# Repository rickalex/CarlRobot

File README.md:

# CarlRobot
A robot named Carl built in a Comm Tech class.

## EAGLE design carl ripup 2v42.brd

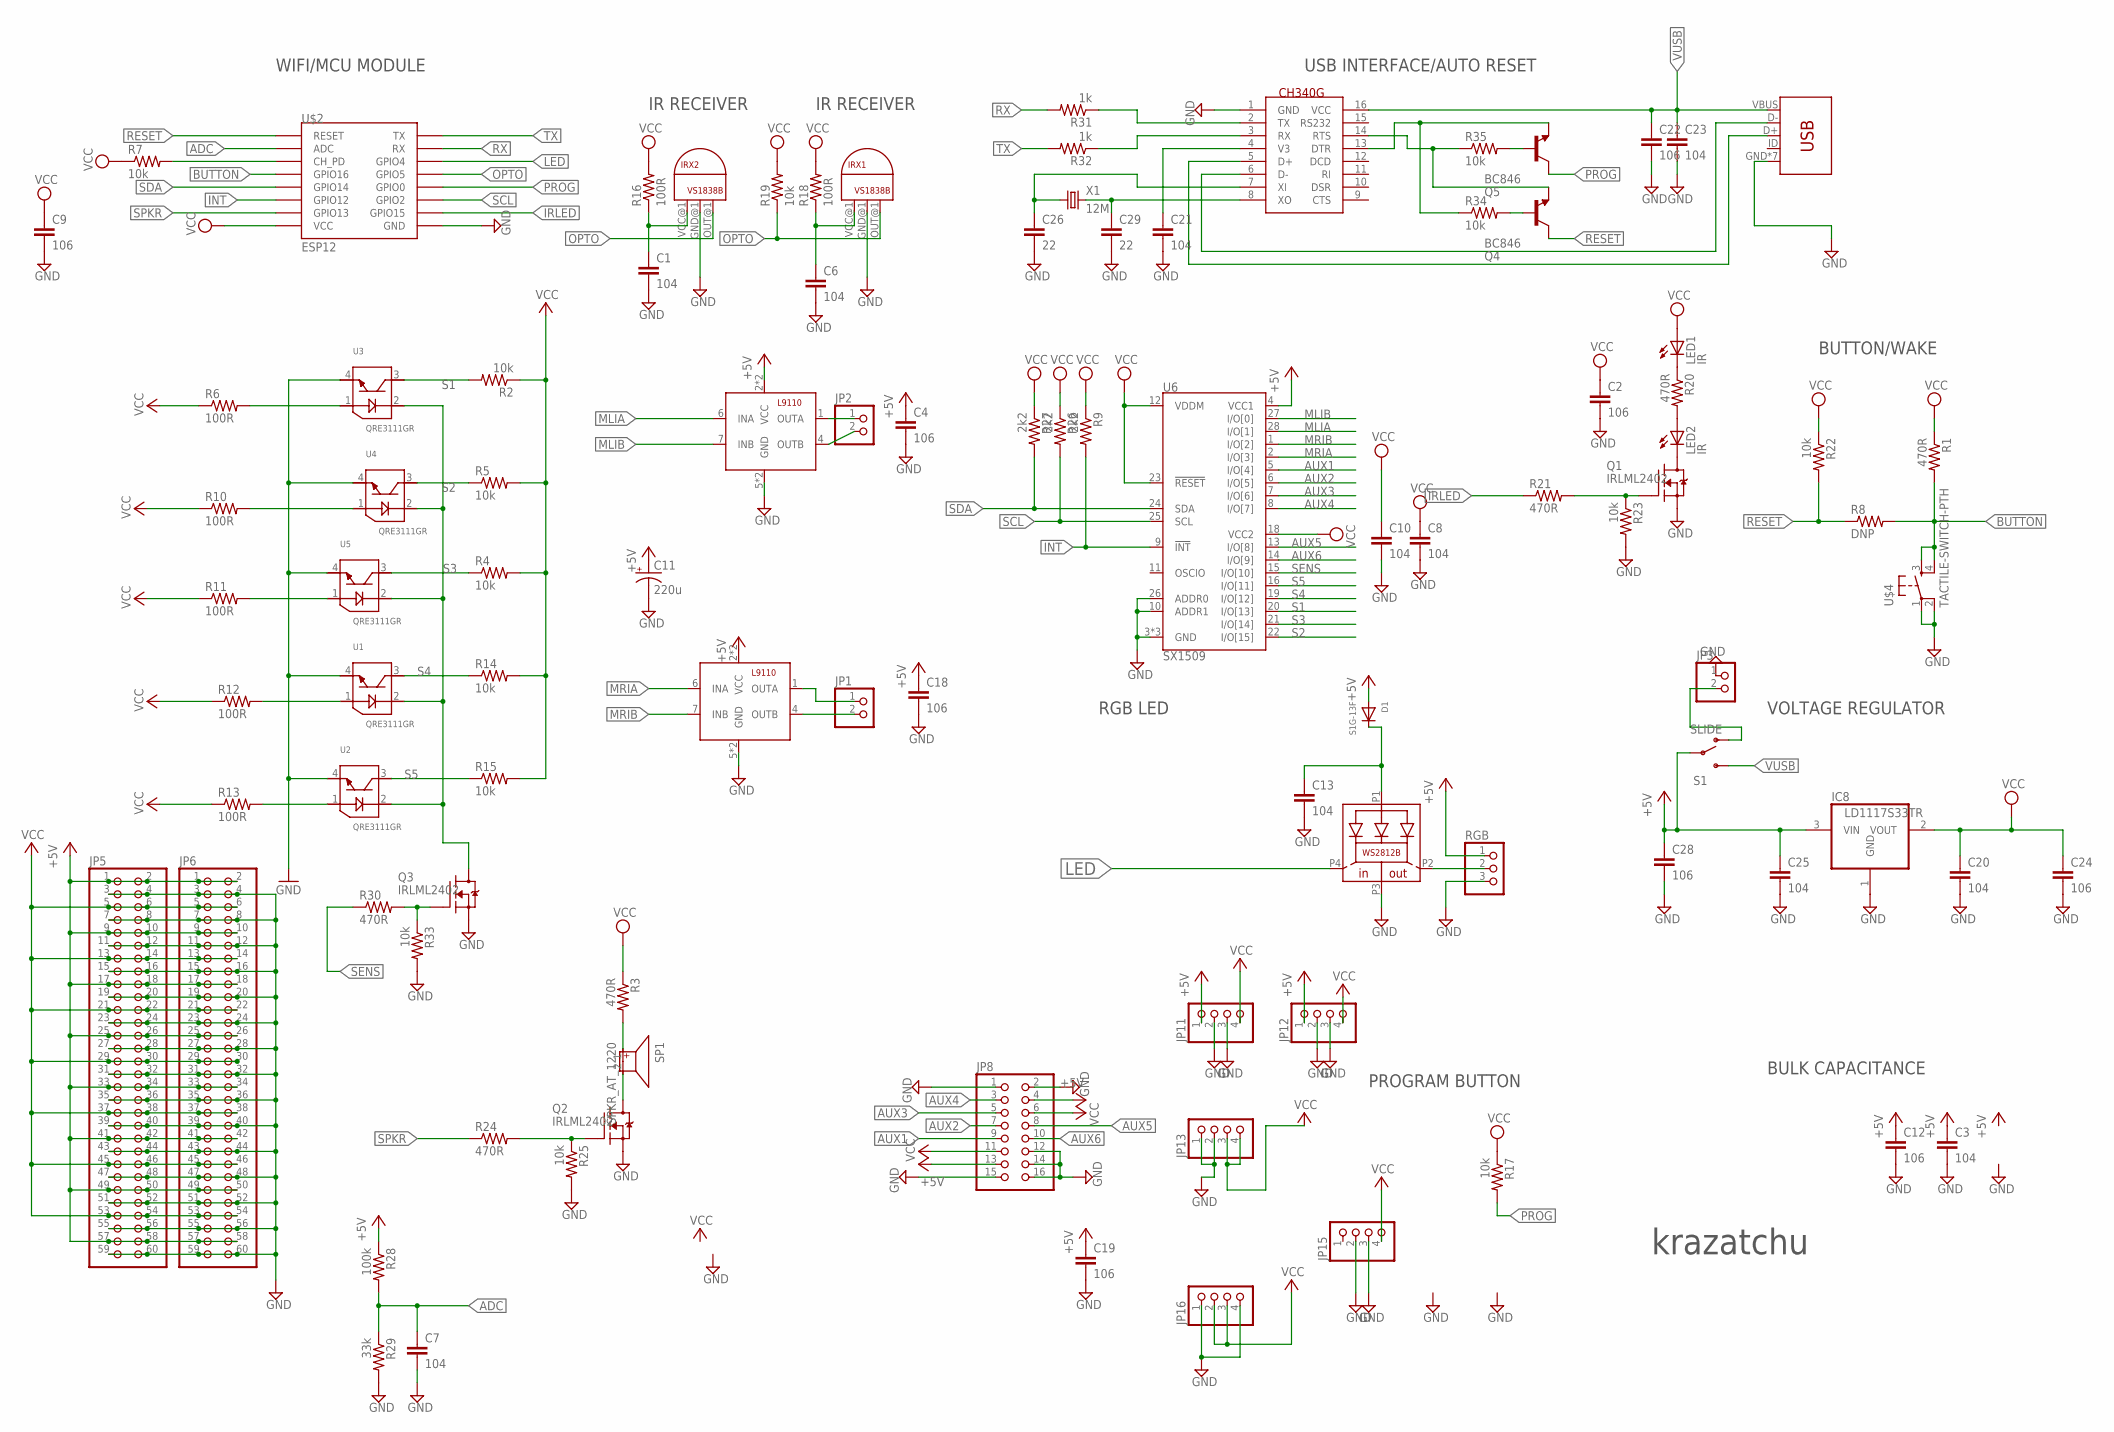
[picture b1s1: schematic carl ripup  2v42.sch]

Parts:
C1, C3, C6, C7, C8, C10, C13, C20, C21, C23, C25: 104; C0805
C2, C4, C9, C12, C18, C19, C22, C24, C28: 106; C0805
C11: 220u; 140CLH-0810
C26, C29: 22; C0805
D1: S1G-13F; SMADIODE
IC1, IC2: L9110; SOIC8
IC8: LD1117S33TR; SOT223
IRX1, IRX2: VS1838B; IR-RX-SINGLE
JP1, JP2, JP3: PINHD-1X2; 1X02
JP5, JP6: PINHD-2X30; 2X30
JP8: PINHD-2X8; 2X08
JP11, JP12, JP13, JP15, JP16: PINHD-1X4; 1X04
LED1, LED2: IR; LED5MM
Q1, Q2, Q3: IRLML2402; SOT23
Q4, Q5: BC846; SOT23
R1, R3, R20, R21, R24, R30: 470R; R0805
R2, R4, R5, R7, R14, R15, R17, R19, R22, R23, R25, R33, R34, R35: 10k; R0805
R6, R10, R11, R12, R13, R16, R18: 100R; R0805
R8: DNP; R0805
R9, R26, R27: 2k2; R0805
R28: 100k; R0805
R29: 33k; R0805
R31, R32: 1k; R0805
RGB: PINHD-1X3RND; 1X03_ROUND
RGB1: ws2812b; PLCC_4_5050_TRIM
S1: SLIDE; SWITCH-SPDT
SP1: SPKR_AT_1220; TRANSDUCER_12/6
U1, U2, U3, U4, U5: QRE3111GR; QRE1113GR
U6: SX1509; QFN-28
U$2: ESP12
U$4: TACTILE-SWITCH-PTH; TAC-SWITCH-PTH
U$5: CH340G; SOIC16
USB1: USB_MICROB-10118194-0001LF; USB-MICRO-B
X1: 12M; HC49UP

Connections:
+5V: C3.1, C4.1, C11.+, C12.1, C18.1, C19.1, C25.1, C28.1, D1.A, IC1.2 (VCC), IC1.3 (VCC), IC2.2 (VCC), IC2.3 (VCC), IC8.3 (VIN), JP5.1, JP5.2, JP5.9, JP5.10, JP5.17, JP5.18, JP5.25, JP5.26, JP5.33, JP5.34, JP5.41, JP5.42, JP5.49, JP5.50, JP5.57, JP5.58, JP6.1, JP6.2, JP6.9, JP6.10, JP6.17, JP6.18, JP6.25, JP6.26, JP6.33, JP6.34, JP6.41, JP6.42, JP6.49, JP6.50, JP6.57, JP6.58, JP8.4, JP8.13, JP11.1, JP12.1, R28.1, RGB.1, S1.2, U6.4 (VCC1)
ADC: C7.1, R28.2, R29.1, U$2.ADC
AUX1: JP8.9, U6.5 (I/O[4])
AUX2: JP8.7, U6.6 (I/O[5])
AUX3: JP8.5, U6.7 (I/O[6])
AUX4: JP8.3, U6.8 (I/O[7])
AUX5: JP8.8, U6.13 (I/O[8])
AUX6: JP8.10, U6.14 (I/O[9])
BUTTON: R1.2, R8.2, U$2.GPIO16, U$4.3, U$4.4
GND: C1.2, C2.2, C3.2, C4.2, C6.2, C7.2, C8.2, C9.2, C10.2, C11.-, C12.2, C13.2, C18.2, C19.2, C20.2, C21.2, C22.2, C23.2, C24.2, C25.2, C26.2, C28.2, C29.2, IC1.5 (GND), IC1.8 (GND), IC2.5 (GND), IC2.8 (GND), IC8.1 (GND), IRX1.GND@1 (GND), IRX2.GND@1 (GND), JP3.1, JP5.3, JP5.4, JP5.7, JP5.8, JP5.11, JP5.12, JP5.15, JP5.16, JP5.19, JP5.20, JP5.23, JP5.24, JP5.27, JP5.28, JP5.31, JP5.32, JP5.35, JP5.36, JP5.39, JP5.40, JP5.43, JP5.44, JP5.47, JP5.48, JP5.51, JP5.52, JP5.55, JP5.56, JP5.59, JP5.60, JP6.3, JP6.4, JP6.7, JP6.8, JP6.11, JP6.12, JP6.15, JP6.16, JP6.19, JP6.20, JP6.23, JP6.24, JP6.27, JP6.28, JP6.31, JP6.32, JP6.35, JP6.36, JP6.39, JP6.40, JP6.43, JP6.44, JP6.47, JP6.48, JP6.51, JP6.52, JP6.55, JP6.56, JP6.59, JP6.60, JP8.1, JP8.2, JP8.12, JP8.14, JP8.15, JP8.16, JP11.2, JP11.3, JP12.2, JP12.3, JP13.1, JP13.2, JP15.2, JP15.3, JP16.1, JP16.4, Q1.2 (S), Q2.2 (S), Q3.2 (S), R23.2, R25.2, R29.2, R33.2, RGB.3, RGB1.P3 (GND), U1.4, U2.4, U3.4, U4.4, U5.4, U6.3 (GND), U6.10 (ADDR1), U6.17 (GND), U6.26 (ADDR0), U6.29 (GND), U$2.GND, U$4.1, U$4.2, U$5.1 (GND), USB1.GND, USB1.MT1 (GND), USB1.MT2 (GND), USB1.MT3 (GND), USB1.MT4 (GND), USB1.SMT3 (GND), USB1.SMT4 (GND)
INT: R9.2, U6.9 (!INT), U$2.GPIO12
IRLED: R21.1, U$2.GPIO15
LED: RGB1.P4 (DI), U$2.GPIO4
MLIA: IC1.6 (INA), U6.28 (I/O[1])
MLIB: IC1.7 (INB), U6.27 (I/O[0])
MRIA: IC2.6 (INA), U6.2 (I/O[3])
MRIB: IC2.7 (INB), U6.1 (I/O[2])
unnamed: R7.2, U$2.CH_PD
unnamed: R6.2, U3.1
unnamed: C1.1, IRX2.VCC@1 (VCC), R16.1
unnamed: C13.1, D1.C, RGB1.P1 (LEDVDD)
unnamed: R3.2, SP1.1
unnamed: Q3.3 (D), U1.2, U2.2, U3.2, U4.2, U5.2
unnamed: Q2.3 (D), SP1.2
unnamed: Q3.1 (G), R30.2, R33.1
unnamed: IC2.4 (OUTB), JP1.2
unnamed: R10.2, U4.1
unnamed: R11.2, U5.1
unnamed: R13.2, U2.1
unnamed: R12.2, U1.1
unnamed: IC2.1 (OUTA), JP1.1
unnamed: JP3.2, S1.1 (O)
unnamed: LED1.K (C), R20.1
unnamed: Q2.1 (G), R24.2, R25.1
unnamed: C6.1, IRX1.VCC@1 (VCC), R18.1
unnamed: IC1.1 (OUTA), JP2.1
unnamed: IC1.4 (OUTB), JP2.2
unnamed: RGB.2, RGB1.P2 (DO)
unnamed: LED2.A, R20.2
unnamed: LED2.K (C), Q1.3 (D)
unnamed: Q1.1 (G), R21.2, R23.1
unnamed: U$5.6 (D-), USB1.D-
unnamed: U$5.5 (D+), USB1.D+
unnamed: C26.1, U$5.7 (XI), X1.1
unnamed: C29.1, U$5.8 (XO), X1.2
unnamed: C21.1, U$5.4 (V3)
unnamed: R31.1, U$5.2 (TX)
unnamed: R32.1, U$5.3 (RX)
unnamed: Q4.2 (E), R35.1, U$5.14 (RTS)
unnamed: Q4.1 (B), R34.2
unnamed: Q5.1 (B), R35.2
unnamed: Q5.2 (E), R34.1, U$5.13 (DTR)
OPTO: IRX1.OUT@1 (OUT), IRX2.OUT@1 (OUT), R19.1, U$2.GPIO5
PROG: Q5.3 (C), R17.2, U$2.GPIO0
RESET: Q4.3 (C), R8.1, R22.2, U$2.RESET
RX: R31.2, U$2.RX
S1: R2.2, U3.3, U6.20 (I/O[13])
S2: R5.1, U4.3, U6.22 (I/O[15])
S3: R4.1, U5.3, U6.21 (I/O[14])
S4: R14.1, U1.3, U6.19 (I/O[12])
S5: R15.1, U2.3, U6.16 (I/O[11])
SCL: R26.2, U6.25 (SCL), U$2.GPIO2
SDA: R27.2, U6.24 (SDA), U$2.GPIO14
SENS: R30.1, U6.15 (I/O[10])
SPKR: R24.1, U$2.GPIO13
TX: R32.2, U$2.TX
VCC: C2.1, C8.1, C9.1, C10.1, C20.1, C24.1, IC8.2 (VOUT), JP5.5, JP5.6, JP5.13, JP5.14, JP5.21, JP5.22, JP5.29, JP5.30, JP5.37, JP5.38, JP5.45, JP5.46, JP5.53, JP5.54, JP6.5, JP6.6, JP6.13, JP6.14, JP6.21, JP6.22, JP6.29, JP6.30, JP6.37, JP6.38, JP6.45, JP6.46, JP6.53, JP6.54, JP8.6, JP8.11, JP11.4, JP12.4, JP13.3, JP13.4, JP15.4, JP16.2, JP16.3, LED1.A, R1.1, R2.1, R3.1, R4.2, R5.2, R6.1, R7.1, R9.1, R10.1, R11.1, R12.1, R13.1, R14.2, R15.2, R16.2, R17.1, R18.2, R19.2, R22.1, R26.1, R27.1, U6.12 (VDDM), U6.18 (VCC2), U6.23 (!RESET), U$2.VCC
VUSB: C22.1, C23.1, S1.3 (S), U$5.16 (VCC), USB1.VBUS

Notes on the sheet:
WIFI/MCU MODULE
USB INTERFACE/AUTO RESET
VOLTAGE REGULATOR
BUTTON/WAKE
RGB LED
PROGRAM BUTTON
BULK CAPACITANCE
krazatchu
IR RECEIVER

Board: 2 copper layers, 97 parts (0 on the bottom side), 68 nets, no tracks yet.

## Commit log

2015-11-06 Added files
    I have no idea how to use this...
2015-11-06 Added apk folder
2015-11-06 Added Android Studio webview project
2015-11-16 Update LICENSE
2016-06-17 Carl Robotics Gerber files 1v41 OSH
2016-06-17 car 2v42.brd

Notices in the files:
parts and their libraries:
SparkFun-DigitalIC: Licensing: Creative Commons ShareAlike 4.0 International - https://creativecommons.org/licenses/by-sa/4.0
